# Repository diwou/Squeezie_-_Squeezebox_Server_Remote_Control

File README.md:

# Squeezie

ESP32-S3-basierte Fernsteuerung für einen Lyrion/Squeezebox-Medienserver mit ILI9488 3,5" Touchdisplay.

## Projekt-Metadaten

- **Repository**: https://codeberg.org/diwou/Squeezie_-_Squeezebox_Server_Remote_Control
- **Lizenz**: CC BY-NC-SA 4.0
- **Version**: v0.5.0

## Hardware

| Komponente | Modell |
|---|---|
| Mikrocontroller | ESP32-S3-WROOM1-N16R8 (16 MB Flash, 8 MB PSRAM) |
| Display | TN 3,5" ILI9488 SPI-TFT 480×320 |
| Touch | XPT2046 (auf Display-Modul integriert) |

### Platine

## Verkabelung

Das Display-Modul hat 14 Pins. Display-SPI und Touch-SPI sind auf getrennte GPIOs gelegt.

| Display-Pin | Bezeichnung | ESP32-S3 GPIO | Hinweis |
|---|---|---|---|
| 1 | VCC | 3,3 V | Spannungsversorgung |
| 2 | GND | GND | Masse |
| 3 | CS | GPIO 17 | LCD Chip Select |
| 4 | RST | GPIO 18 | LCD Reset |
| 5 | DC/OC | GPIO 9 | Data/Command |
| 6 | SDI | GPIO 3 | Display MOSI |
| 7 | SCK | GPIO 46 | Display SPI-Takt |
| 8 | BL | GPIO 9 | Hintergrundbeleuchtung (HIGH = an) |
| 9 | SDO | GPIO 10 | Display MISO (optional) |
| 10 | TCK | GPIO 11 | Touch SPI-Takt |
| 11 | TCS | GPIO 12 | Touch Chip Select |
| 12 | TDI | GPIO 13 | Touch MOSI |
| 13 | TDO | GPIO 14 | Touch MISO |
| 14 | PEN | GPIO 21 | Touch-Interrupt (IRQ) |

## Software-Einrichtung

### Voraussetzungen

- [PlatformIO](https://platformio.org/) (VSCodium/VSCode Extension oder CLI)

### Erstmalige Einrichtung

```bash
# Bibliotheken installieren und kompilieren
pio run

# Auf den ESP32 flashen (USB angeschlossen)
pio run --target upload

# Serielle Konsole öffnen
pio device monitor
```

### WLAN-Konfiguration

Beim ersten Start öffnet das Gerät einen Access Point **Squeezie-Setup**. Im Browser
`192.168.4.1` aufrufen und WLAN-Zugangsdaten eingeben. Nach dem Verbinden mit dem
Heimnetz erscheint die IP-Adresse auf dem Display.

### Touch-Kalibrierung

Beim allerersten Start erscheint automatisch die Kalibrierung. Es werden 3 Kreuzmarkierungen
nacheinander angezeigt, die mit dem Finger berührt werden müssen.

Die Kalibrierungsdaten werden im NVS (Flash) gespeichert und bei jedem Neustart geladen.

**Neu kalibrieren:** Obere linke Ecke des Displays 3 Sekunden gedrückt halten.

## Aktueller Stand — v0.5.0

### Player-Screen (Touch-Display)

- **Cover-Art** (128×128 px, vom LMS-Server geladen)
- **Titelanzeige**: Titel (scrollend), Interpret, Album, Tracknummer / Gesamtdauer
- **Fortschrittsbalken** mit Zeitanzeige, antippen zum Seekten
- **Transport-Buttons**: |< / Pause/Play / >|
- **Lautstärke**: Balken mit [−] / [+], Halten wiederholt
- **Gruppenlautstärke**: Bei synchronisierten Lyrion-Playern werden Lautstärkeänderungen auf die ganze Sync-Gruppe angewendet und lassen sich in den Einstellungen ein- oder ausschalten
- **Modus-Buttons**: Wiederholen (aus / Titel / Liste) und Zufall (an/aus)
- **Uhrzeit** (NTP) in der Statuszeile
- **Einstellungs-Screen**: Server-Suche per UDP-Discovery, Player-Auswahl, Sync-Lautstärke-Schalter

### Webinterface (Browser)

- **Player-Steuerung** (`http://<ip>/`): Titel, Cover, Fortschrittsbalken, Transport, Lautstärke, Modus
- **Einstellungen** (`/settings`): WLAN, Netzwerk (DHCP/Statisch), NTP, Squeezebox-Server, Player-Auswahl
- **OTA-Firmware-Update** (`/update`)
- **Log** (`/log`): Ring-Buffer mit den letzten 20 Systemereignissen

### Technisches

- **Lyrion/Squeezebox JSON-RPC API**: Play/Pause/Next/Prev/Seek/Lautstärke/Wiederholen/Zufall
- **Server-Discovery**: UDP Slim-Discovery auf Port 3483, mDNS-Service-Discovery als Fallback
- **NVS-Persistenz**: alle Einstellungen überleben einen Neustart
- **Cover-Download**: asynchroner FreeRTOS-Task (blockiert die Main-Loop nicht)
- **Selektives Display-Rendering**: nur geänderte Felder werden neu gezeichnet

## Web-Firmware-Installer (Codeberg Page)

Der Firmware-Installer über Browser ist auf der Codeberg-Page verfügbar:

- [Web-Installer öffnen](https://diwou.codeberg.page/Squeezie_-_Squeezebox_Server_Remote_Control/)

## Geplante Funktionen

- [ ] IR-Fernbedienung (Hardware-Erweiterung)

## Lizenz

[CC BY-NC-SA 4.0](https://creativecommons.org/licenses/by-nc-sa/4.0/) — Namensnennung,
nicht-kommerziell, Weitergabe unter gleichen Bedingungen.

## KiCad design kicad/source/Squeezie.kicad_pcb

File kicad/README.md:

# KiCad Hardware

Dieses Verzeichnis enthält die Platinenquellen und die exportierten Fertigungsdaten für Squeezie.

## Struktur

- `source/` - bearbeitbare KiCad-Quellen für Revision `rev0.1`
- `fab/rev0.1/bom/` - BOM, Designatoren, Positionen und Netlist
- `fab/rev0.1/Squeezie_Squeezseboxserver_Control_0.1.zip` - komplettes Fertigungspaket für den Bestelldienstleister

## Kurz-BOM

_Abgeleitet aus `fab/rev0.1/bom/bom.csv`. Wenn sich die Platine ändert, diese Übersicht gemeinsam mit der Stückliste prüfen._

| Bereich | Bauteile | Bauform | Menge | Zweck |
|---|---|---|---:|---|
| MCU | `U2` ESP32-S3-WROOM-1 | ESP32-S3-WROOM-1 | 1 | Hauptprozessor, WLAN, Steuerlogik |
| Anzeige / Anschluss | `J1` USB-C, `J2` ILI9488 Display | USB_C_Receptacle_HCTL_HC-TYPE-C-16P-01A, PinSocket_1x14_P2.54mm_Vertical | 2 | USB- und Display-Anschluss |
| Bedienung | `SW1` Boot, `SW2` Reset, `SW3` Prev, `SW4` Next, `SW5` Play, `SW6` Vol-, `SW7` Vol+, `SW8` Mute | SWITCH_FSMARA | 8 | Bedienelemente für den Player |
| Spannungsversorgung | `U1` TLV76133DCY, `D2` SS14, `D1` PWR | SOT-223-3_TabPin2, D_SMA, 0805 | 3 | 3,3-V-Regler, Schutzdiode, Power-LED |
| Widerstände | `R1` 1k, `R2/R3` 5,1k, `R4/R5/R6/R7/R8/R9/R10` 10k | 0805 | 10 | Pullups und Signalbegrenzung |
| Kondensatoren | `C1/C2` 10µ, `C3` 10µ, `C5` 1µ, `C4/C6/C7/C10/C11/C12/C13/C14/C15` 100n | 1206, 0805 | 12 | Abblockung und Pufferung |

## Hinweise

- `H1` bis `H4` sind Montagebohrungen und tauchen deshalb nicht in der BOM-CSV auf.
- Die vollständige, exportierte Stückliste liegt zusätzlich als CSV unter `fab/rev0.1/bom/`.
- `source/*.kicad_prl` und `source/fp-info-cache` sind lokale bzw. generierte Dateien und werden per `.gitignore` ausgeschlossen.
- Das Projekt wird im gleichen Schema gepflegt wie der HUB75-KiCad-Stand.

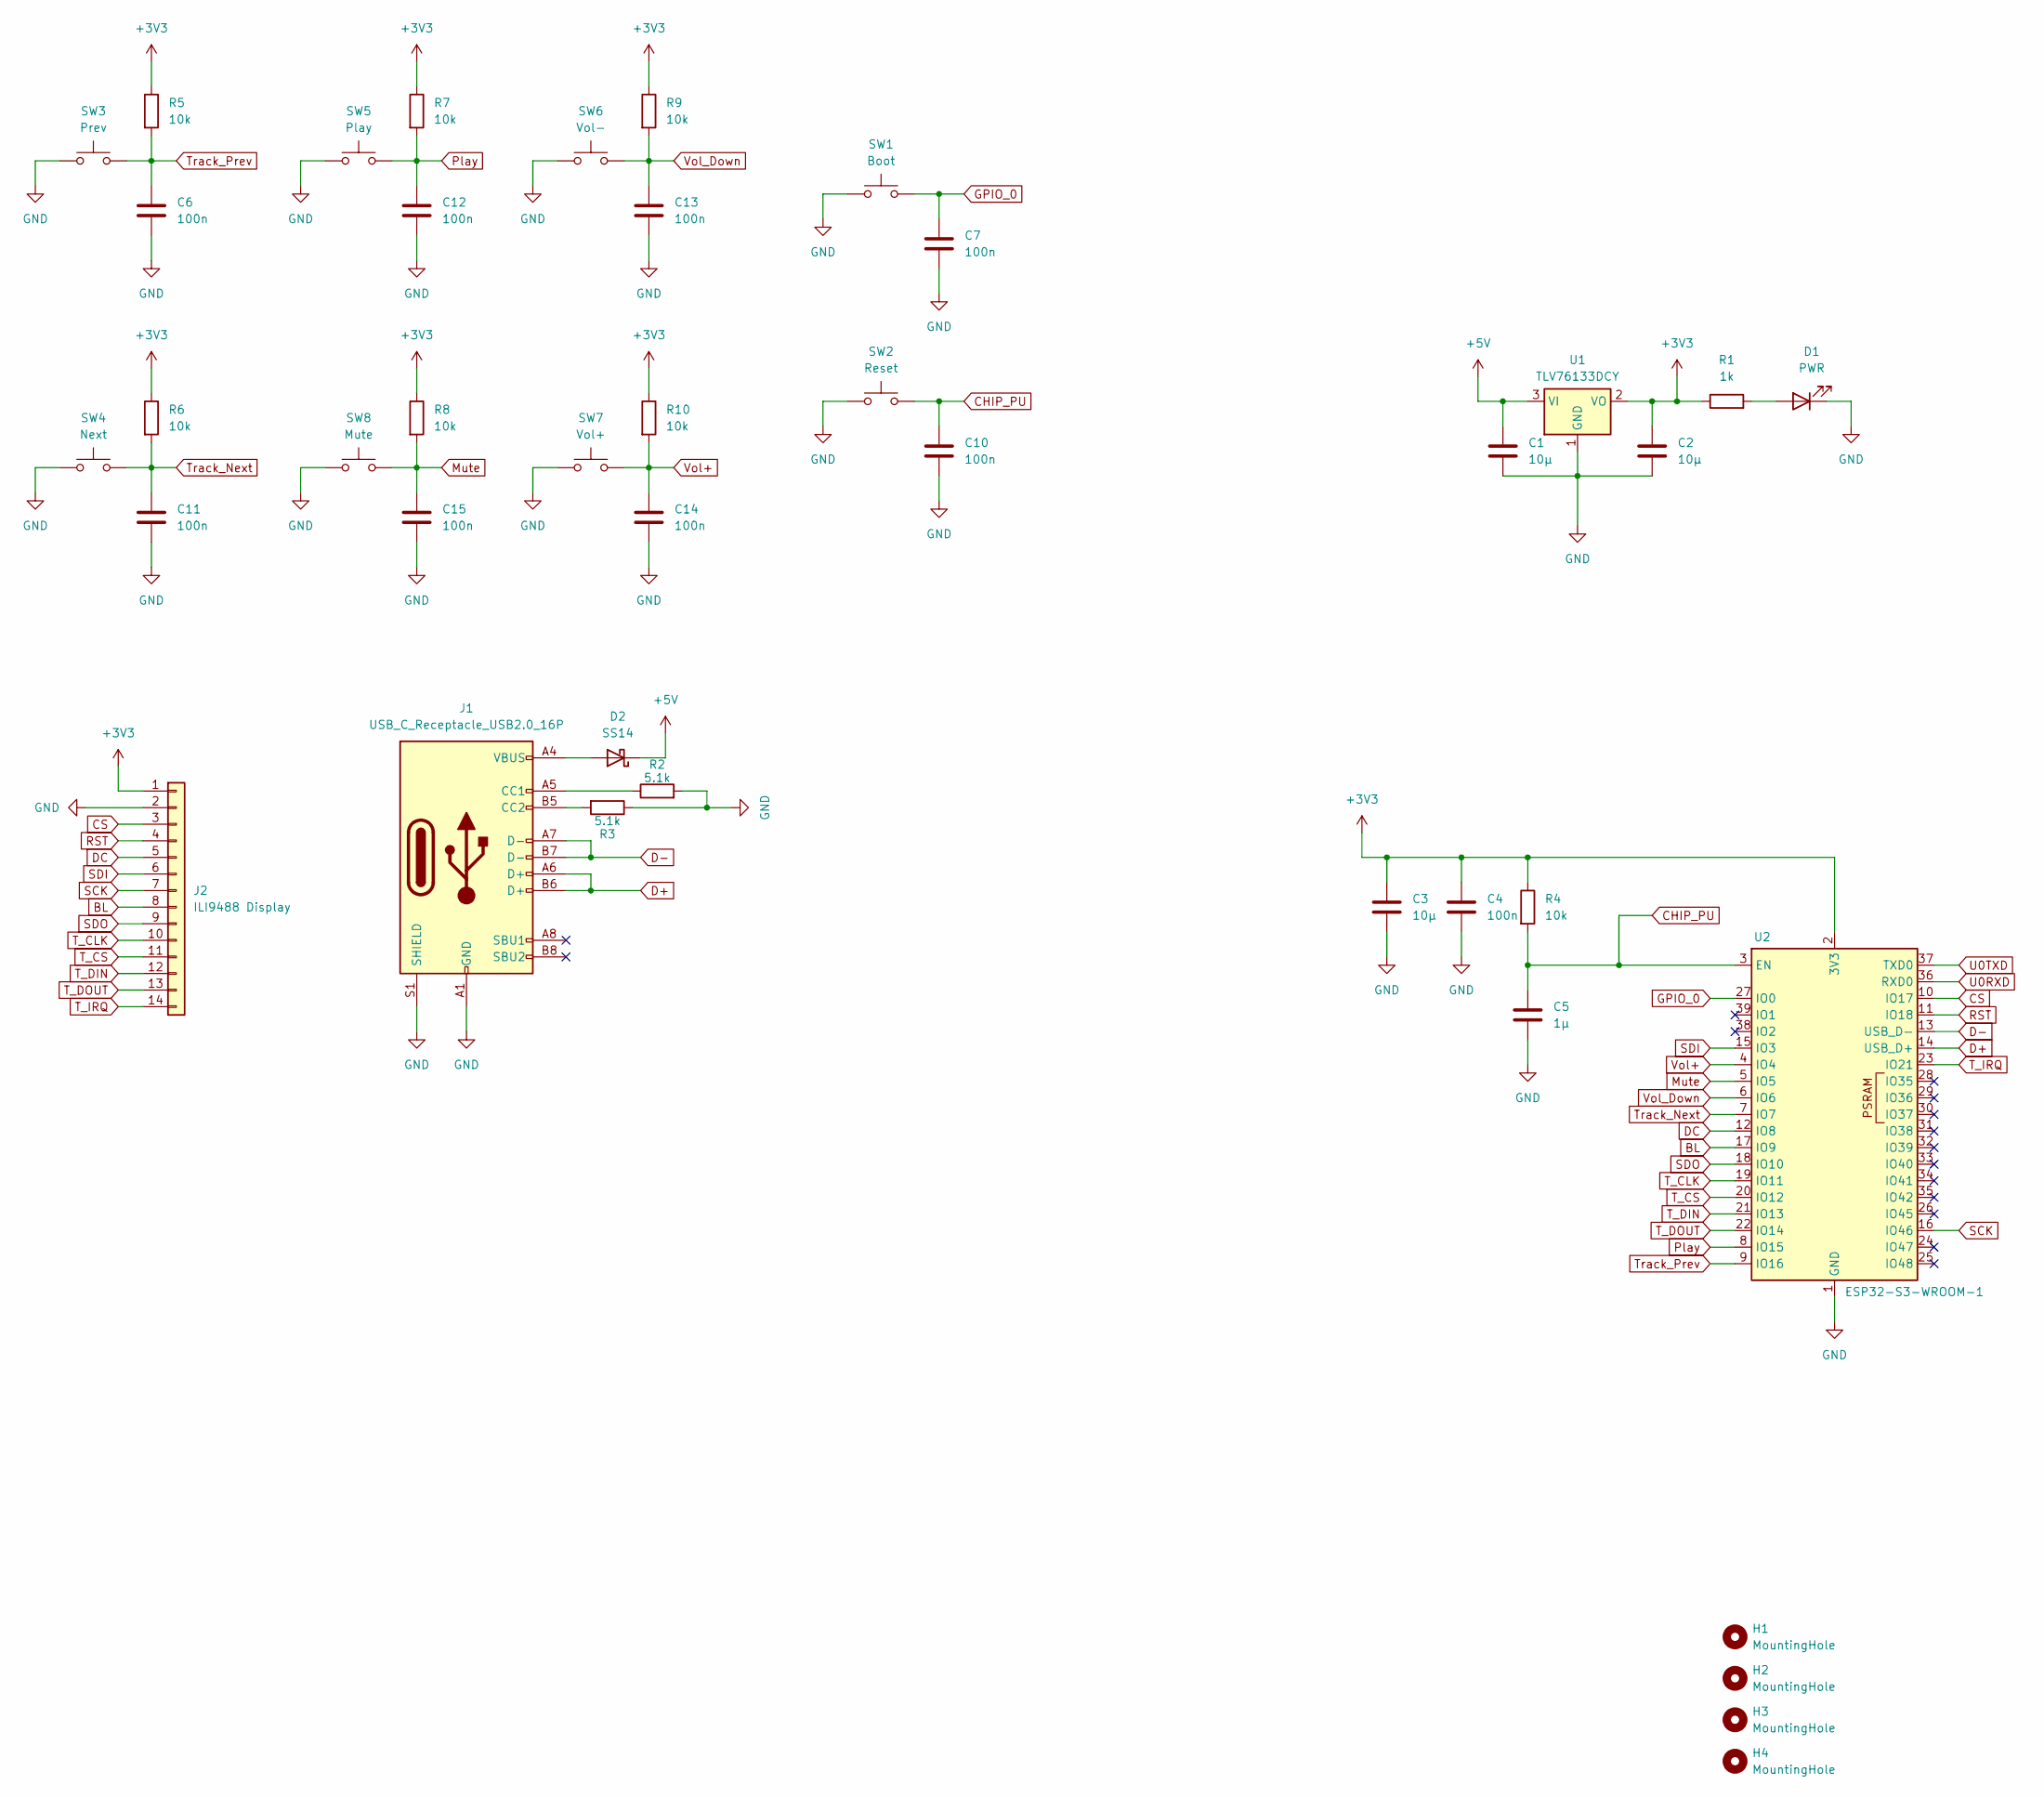
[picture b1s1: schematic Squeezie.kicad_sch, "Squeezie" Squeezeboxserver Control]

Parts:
C1, C2: 10µ; C_1206_3216Metric_Pad1.33x1.80mm_HandSolder
C3: 10µ; C_0805_2012Metric_Pad1.18x1.45mm_HandSolder
C4, C6, C7, C10, C11, C12, C13, C14, C15: 100n; C_0805_2012Metric_Pad1.18x1.45mm_HandSolder
C5: 1µ; C_0805_2012Metric_Pad1.18x1.45mm_HandSolder
D1: PWR; LED_0805_2012Metric_Pad1.15x1.40mm_HandSolder
D2: SS14; D_SMA
H1, H2, H3, H4: MountingHole; MountingHole_3.5mm
J1: USB_C_Receptacle_USB2.0_16P; USB_C_Receptacle_HCTL_HC-TYPE-C-16P-01A
J2: ILI9488 Display; PinSocket_1x14_P2.54mm_Vertical
R1: 1k; R_0805_2012Metric_Pad1.20x1.40mm_HandSolder
R2, R3: 5.1k; R_0805_2012Metric_Pad1.20x1.40mm_HandSolder
R4, R5, R6, R7, R8, R9, R10: 10k; R_0805_2012Metric_Pad1.20x1.40mm_HandSolder
SW1: Boot; SWITCH_FSMARA
SW2: Reset; SWITCH_FSMARA
SW3: Prev; SWITCH_FSMARA
SW4: Next; SWITCH_FSMARA
SW5: Play; SWITCH_FSMARA
SW6: Vol-; SWITCH_FSMARA
SW7: Vol+; SWITCH_FSMARA
SW8: Mute; SWITCH_FSMARA
U1: TLV76133DCY; SOT-223-3_TabPin2
U2: ESP32-S3-WROOM-1

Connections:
+3V3: C2.1, C3.1, C4.1, J2.1, R1.1, R4.1, R5.1, R6.1, R7.1, R8.1, R9.1, R10.1, U1.2 (VO), U2.2 (3V3)
+5V: C1.1, D2.1 (K), U1.3 (VI)
BL: J2.8, U2.17 (IO9)
CHIP_PU: C5.1, C10.1, R4.2, SW2.2, U2.3 (EN)
CS: J2.3, U2.10 (IO17)
D+: J1.A6 (D+), J1.B6 (D+), U2.14 (USB_D+)
D-: J1.A7 (D-), J1.B7 (D-), U2.13 (USB_D-)
DC: J2.5, U2.12 (IO8)
GND: C1.2, C2.2, C3.2, C4.2, C5.2, C6.2, C7.2, C10.2, C11.2, C12.2, C13.2, C14.2, C15.2, D1.1 (K), J1.A1 (GND), J1.A12 (GND), J1.B1 (GND), J1.B12 (GND), J1.S1 (SHIELD), J2.2, R2.2, R3.1, SW1.1, SW1.GND, SW2.1, SW2.GND, SW3.1, SW3.GND, SW4.1, SW4.GND, SW5.1, SW5.GND, SW6.1, SW6.GND, SW7.1, SW7.GND, SW8.1, SW8.GND, U1.1 (GND), U2.1 (GND), U2.40 (GND), U2.41 (GND)
GPIO_0: C7.1, SW1.2, U2.27 (IO0)
Mute: C15.1, R8.2, SW8.2, U2.5 (IO5)
unnamed: D1.2 (A), R1.2
unnamed: D2.2 (A), J1.A4 (VBUS), J1.A9 (VBUS), J1.B4 (VBUS), J1.B9 (VBUS)
unnamed: J1.A5 (CC1), R2.1
unnamed: J1.B5 (CC2), R3.2
Play: C12.1, R7.2, SW5.2, U2.8 (IO15)
RST: J2.4, U2.11 (IO18)
SCK: J2.7, U2.16 (IO46)
SDI: J2.6, U2.15 (IO3)
SDO: J2.9, U2.18 (IO10)
T_CLK: J2.10, U2.19 (IO11)
T_CS: J2.11, U2.20 (IO12)
T_DIN: J2.12, U2.21 (IO13)
T_DOUT: J2.13, U2.22 (IO14)
T_IRQ: J2.14, U2.23 (IO21)
Track_Next: C11.1, R6.2, SW4.2, U2.7 (IO7)
Track_Prev: C6.1, R5.2, SW3.2, U2.9 (IO16)
U0RXD: U2.36 (RXD0)
U0TXD: U2.37 (TXD0)
Vol+: C14.1, R10.2, SW7.2, U2.4 (IO4)
Vol_Down: C13.1, R9.2, SW6.2, U2.6 (IO6)

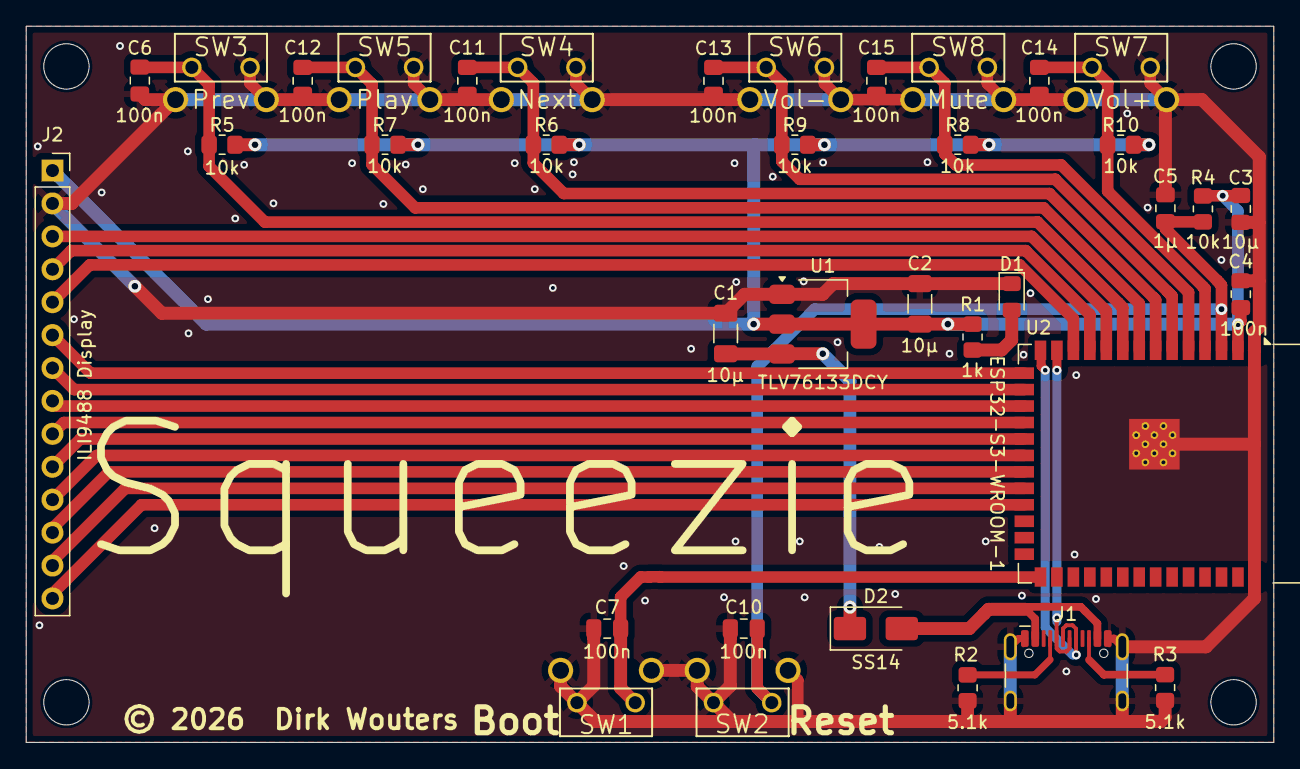
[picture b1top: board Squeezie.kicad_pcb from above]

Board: 2 copper layers, 96.3 x 55.3 mm, 41 parts (0 on the bottom side), 29 nets.

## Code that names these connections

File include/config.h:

#pragma once

// =============================================================================
// Squeezie — Zentrale Konfiguration
// =============================================================================

// --- Anwendung ---
#define APP_VERSION_BASE "0.5.0"
#if __has_include("version_generated.h")
#include "version_generated.h"
#endif
#ifndef APP_VERSION
#define APP_VERSION APP_VERSION_BASE
#endif

// --- Pins ---
#define PIN_TFT_BL      9   // Hintergrundbeleuchtung (HIGH = an)
#define PIN_TFT_CS      17  // Display Chip-Select
#define PIN_TFT_DC      8   // Display Data/Command
#define PIN_TFT_RST     18  // Display Reset
#define PIN_TFT_MOSI    3   // Display SDI / MOSI (SPI)
#define PIN_TFT_MISO    10  // Display SDO / MISO (SPI, optional read-back)
#define PIN_TFT_SCLK    46  // Display SCK (SPI)
#define PIN_TOUCH_CS    12  // Touch Chip-Select (TCS)
#define PIN_TOUCH_IRQ   21  // Touch-Interrupt (PEN, LOW = berührt)
#define PIN_TOUCH_MOSI  13  // Touch T_DIN / MOSI (SPI)
#define PIN_TOUCH_MISO  14  // Touch T_DOUT / MISO (SPI)
#define PIN_TOUCH_SCLK  11  // Touch T_CLK / SCK (SPI)
#define PIN_BOOT_BTN    0   // Eingebauter BOOT-Button (LOW = gedrückt)
#define PIN_PLAY_BTN    15  // Externer Play/Pause-Taster (LOW = gedrückt)
#define PIN_PREV_BTN    16  // Externer Track-zurueck-Taster (LOW = gedrückt)
#define PIN_NEXT_BTN    7   // Externer Track-vor-Taster (LOW = gedrückt)
#define PIN_VOL_UP_BTN  4   // Externer Volume-Plus-Taster (LOW = gedrückt)
#define PIN_VOL_DN_BTN  6   // Externer Volume-Minus-Taster (LOW = gedrückt)
#define PIN_MUTE_BTN    5   // Externer Mute-Taster (LOW = gedrückt)

// --- Display ---
#define DISPLAY_ROTATION    1   // 1 = Querformat: 480×320
#define DISPLAY_WIDTH     480
#define DISPLAY_HEIGHT    320

// --- NVS ---
#define NVS_NAMESPACE        "squeezie"
#define NVS_KEY_CAL_OK       "calOK"    // bool: Kalibrierung gültig
#define NVS_KEY_CAL_X0       "calX0"    // int16: Rohwert Bildschirm-X am linken Zielpunkt
#define NVS_KEY_CAL_X1       "calX1"    // int16: Rohwert Bildschirm-X am rechten Zielpunkt
#define NVS_KEY_CAL_Y0       "calY0"    // int16: Rohwert Bildschirm-Y am oberen Zielpunkt
#define NVS_KEY_CAL_Y1       "calY1"    // int16: Rohwert Bildschirm-Y am unteren Zielpunkt
#define NVS_KEY_CAL_SWAP     "calSwap"  // uint8: 1 = X/Y-Kanäle getauscht

// --- Kalibrierungszielpunkte (Bildschirmkoordinaten) ---
#define CAL_X_LEFT    30
#define CAL_X_RIGHT   (DISPLAY_WIDTH  - 30)
#define CAL_Y_TOP     30
#define CAL_Y_BOTTOM  (DISPLAY_HEIGHT - 30)

// --- WiFi / Netzwerk (NVS-Schlüssel) ---
#define NVS_KEY_WIFI_SSID   "wifiSSID"
#define NVS_KEY_WIFI_PASS   "wifiPass"
#define NVS_KEY_NET_DHCP    "netDHCP"
#define NVS_KEY_NET_IP      "netIP"
#define NVS_KEY_NET_MASK    "netMask"
#define NVS_KEY_NET_GW      "netGW"
#define NVS_KEY_NET_DNS     "netDNS"
#define NVS_KEY_NET_NTP     "netNTP"

// --- Squeezebox Server (NVS-Schlüssel) ---
#define NVS_KEY_SRV_HOST    "srvHost"
#define NVS_KEY_SRV_PORT    "srvPort"
#define NVS_KEY_PLAYER_MAC  "playerMAC"
#define NVS_KEY_SYNC_VOL    "syncVol"
#define NVS_KEY_SCROLL_SPD  "scrollSpd"
#define NVS_KEY_PL_ID       "plId"
#define NVS_KEY_PL_NAME     "plName"

// --- WiFi AP ---
#define WIFI_AP_SSID             "Squeezie-Setup"
#define WIFI_CONNECT_TIMEOUT_MS  8000
#define LYRION_DEFAULT_PORT      9000

// --- OTA / Sicherheit ---
#define OTA_HOSTNAME             "squeezie"
#define OTA_PASSWORD             "squeezie"

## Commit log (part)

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2026-04-05 Initial commit: ESP32-S3 Squeezebox remote control
    ESP32-S3-WROOM1-N16R8 mit ILI9488 3.5" Touchdisplay (LovyanGFX),
    ESPAsyncWebServer, Lyrion/Squeezebox API-Anbindung (in Arbeit).
    Lizenz: CC BY-NC-SA 4.0
2026-04-05 docs: README auf v0.3.2 aktualisiert, Lizenz auf CC BY-NC-SA 4.0
2026-04-05 Factory Reset via BOOT-Button
2026-04-07 Release 0.3.3
2026-04-07 Release 0.4.0
2026-04-07 Clean up release metadata
2026-04-09 Add playlist selection in settings and display mute control
2026-04-11 Fix LMS mute handling and add cspell setup
2026-04-11 Update changelog commit references
2026-04-11 Add automatic firmware export
2026-04-11 Update changelog firmware export reference
2026-04-20 Fix cover stability and document 0.4.2
2026-04-20 Unify development versioning and fix prefetch
2026-04-21 Add configurable sync volume handling
2026-04-22 fix: Bedienung reaktionsschneller machen
2026-04-22 fix: externe Lautstärkeänderungen stabilisieren
2026-04-22 fix: Sync-Player absolut nachführen
2026-04-23 docs: KiCad-Squeezie im HUB75-Schema ablegen
2026-04-23 docs: Changelog-Referenz für KiCad-Import ergänzen
2026-04-25 fix: Cover-Download und Regeln stabilisieren
2026-04-28 PlatformIO stabilisieren
2026-04-29 feat: Code-Review-Punkte umgesetzt
    - display.cpp in 4 Module aufgeteilt (display_draw, display_touch,
    display_cover, display_screens) + interner Header display_intern.h
    - HW-Watchdog (esp_task_wdt_init) in setup() aktiviert
    - Doxygen-Kommentare zu allen öffentlichen API-Headern ergänzt
    - OTA-Passwortschutz über config.h (OTA_PASSWORD) aktiviert
    - NVS-Kalibrierungsdaten: Namespace-Konflikt behoben
2026-04-29 fix: Watchdog-Bootloop durch fehlendes Feeding behoben
    Der HW-Watchdog (esp_task_wdt_init(10, true)) führte zu einem Bootloop,
    weil loop() und coverDlTask() den Watchdog nicht regelmässig feedeten.
    - esp_task_wdt_add(nullptr) + esp_task_wdt_reset() in loop()
    - esp_task_wdt_reset() während readHttpBody() (HTTP-Download)
    - esp_task_wdt_reset() nach HTTP-Download in coverDlTask()
    Referenz: watchdog-bootloop-20260429
2026-04-29 fix: Cover-Download-Task-Handle und Watchdog-Bootloop endgültig behoben
    - in coverDlTask() entfernt: das Task-Handle
    bleibt erhalten, sodass displayPreloadCover() weiterhin Notifications
    senden kann (bisher nur erster Cover-Download funktionierte).
    - coverDlTask() und prefetchTask() auf ulTaskNotifyTake mit 2s-Timeout
    umgestellt: blockierte Tasks mit esp_task_wdt_add() führten nach 10s
    zu Watchdog-Reset → ESP-Reboot-Loop.
2026-04-29 fix: Prefetch vollständig entfernt und Cover-Wechsel-Dedup repariert
    - Prefetch-Mechanismus komplett entfernt (prefetchTask, displayQueuePrefetch,
    PrefetchSlot, PSRAM-Puffer, SQUEEZE_PREFETCH-Konstante), da er wiederholt
    Probleme mit konkurrierenden HTTP-Downloads und Task-Interferenzen verursachte.
    - LMS-Poll fragt nur noch aktuellen Titel ab statt SQUEEZE_PREFETCH+1 Einträge.
    - URL-Dedup in displayPreloadCover() auf URL+Key-Vergleich umgestellt:
    bisher blockierte die identische /music/current/…-URL jeden weiteren
2026-04-29 docs: Changelog-Referenzen auf aktuellen Commit-Hash aktualisiert
2026-04-29 docs: Preload-zu-Notification-Umstellung im Changelog dokumentiert
    - Expliziter Eintrag, dass das Single-Shot-Preload durch persistenten
    Notification-basierten coverDlTask ersetzt wurde.
2026-04-29 fix: OTA-Authentifizierung durch upload_flags in platformio.ini ergänzt
    - upload_flags=--auth=squeezie in der [env:…_ota]-Sektion hinzugefügt,
    damit das OTA-Passwort aus config.h beim Upload mitgesendet wird.
    - Der Code-Review hatte ArduinoOTA.setPassword() aktiviert, aber die
    platformio.ini nicht mit angepasst.
2026-04-29 fix: Single-Shot-Cover-Download wiederhergestellt (Latenz-Probleme)
    - Persistenten Notification-Task (Code-Review) rückgängig gemacht:
    displayPreloadCover() erzeugt wieder einen eigenen FreeRTOS-Task pro
    Cover-Download, der nach der Übertragung terminiert.
    - HTTP-Timeouts auf alte Werte zurückgesetzt (3000ms Gesamt, 1200ms
    pro Read), da die erhöhten Timeouts (8000ms/5000ms) Latenzen
    verursachten.
2026-04-29 docs: Changelog-Hash auf aktuellen Commit aktualisiert
2026-04-29 fix: coverDlTask nicht mehr zum Watchdog hinzugefügt
    - esp_task_wdt_add() aus coverDlTask entfernt: der Single-Shot-Task läuft
    nur kurz (HTTP-Timeout 3s), feedt während readHttpBody() und terminiert
    sich selbst. Ein eigener Watchdog-Eintrag ist nicht nötig und verursachte
    OTA-Abbrüche (der Watchdog erwartete Feeding von einem nicht mehr
    existierenden Task).
2026-04-29 fix: Watchdog-Init nach webserverInit() verschoben
    - esp_task_wdt_init() in setup() steht jetzt erst NACH webserverInit(),
    da connectWiFi() bis zu 12 s blockieren kann (8 s + 4 s Retry).
    Der Watchdog (10 s) hätte während der WLAN-Verbindung in setup()
    einen Neustart ausgelöst.
    - Gegenmassnahme für die zyklischen Reboots und OTA-Abbrüche.
2026-04-29 fix: OTA-Fortschritt entkoppeln
2026-04-29 fix: ArduinoOTA-Watchdog pausieren
2026-04-29 fix: Steuerbefehle schneller priorisieren
2026-05-01 fix: OTA-Anzeige wieder sofort zeichnen
2026-05-01 docs: Changelog-Referenzen und OTA-Fix ergänzen
2026-05-01 fix: Display-Text für türkische Glyphen fallbacken
2026-05-01 docs: Changelog um Display-Glyphen-Fix ergänzen
2026-05-01 fix: Display-Cover auf schnellen Pfad zurücksetzen
2026-05-01 docs: Display-Cover-Fix im Changelog ergänzen
2026-05-01 fix: Lautstärkebuttons im Player-Screen wieder einblenden
2026-05-01 docs: Lautstärke-Buttons im Changelog ergänzen
2026-05-01 fix: Browser-Cover direkt auf 512er LMS-URL umstellen
2026-05-01 docs: Browser-Cover-Fix im Changelog ergänzen
2026-05-01 fix: Browser-Cover und OTA-Layout nachziehen
2026-05-01 docs: Browser-Cover und OTA-Layout im Changelog nachziehen
2026-05-01 fix: Browser-Coverfläche auf 512px erweitern
2026-05-01 fix: Browser-Cover über lokalen Proxy ausliefern
2026-05-01 docs: Browser-Cover-Proxy im Changelog ergänzen
2026-05-01 fix: Browser-Cover wieder direkt vom LMS laden
2026-05-01 docs: Browser-Cover-Fix im Changelog aktualisieren
2026-05-01 fix: Browser-Cover per Redirect auf LMS lenken
2026-05-01 docs: Browser-Redirect im Changelog ergänzen
2026-05-01 fix: Browser-Cover wieder direkt auf 512x512 LMS-URL
2026-05-01 fix: Browser-Cover direkt aus Status-URL speisen
2026-05-01 docs: Browser-Cover direkt aus Status-URL dokumentieren
2026-05-01 fix: Browser-Cover beim Rendern initial setzen
2026-05-01 fix: Browser-Cover im Initial-HTML setzen
2026-05-01 docs: Changelog für Browser-URL nachziehen
2026-05-01 fix: Browser-Cover auf current-URL zurückführen
2026-05-01 fix: Browser-Cover sichtbar laden
2026-05-01 docs: Browser-Cover-Fix im Changelog vermerken
2026-05-01 fix: Browser-Cover-Startwert stabilisieren
2026-05-01 fix: Browser-Cover per JS initialisieren
2026-05-01 docs: Browser-Cover-Startfix dokumentieren
2026-05-01 fix: Browser-Cover wieder direkt setzen
2026-05-01 docs: Browser-Cover-Direktlink dokumentieren
2026-05-01 fix: Browser-Cover als Overlay rendern
2026-05-01 docs: Overlay-Fix im Changelog vermerken
2026-05-01 fix: Browser-Cover über Platzhalter legen
2026-05-01 docs: Browser-Overlay-Fix dokumentieren
2026-05-01 fix: Browser-Cover als Hintergrund laden
2026-05-01 docs: Browser-Hintergrundpfad dokumentieren
2026-05-02 fix: Browser-Cover wieder als Proxy ausliefern
2026-05-03 fix: LMS-Poll für Cover-Updates verkürzen
2026-05-03 docs: Changelog für Poll-Verkürzung referenzieren
2026-05-04 fix: Player-Screen nach Langläufen stabilisieren
2026-05-04 docs: Changelog um Langläufer-Fix ergänzen
2026-05-09 fix: Cover-Downloads bei Timeout beenden
2026-05-09 docs: Changelog um Cover-Fix-Referenz ergänzen
2026-05-12 fix: aktualisiere pinmapping, touch-spi und serversuche
2026-05-12 docs(changelog): ersetze arbeits-ids durch commit-hash
2026-05-12 fix: verbessere lms discovery und erweitere hardware-tasten
2026-05-12 docs(changelog): hinterlege commit-id fuer neue eintraege
2026-05-12 feat: release-vorbereitung mit web-installer und discovery-fixes
2026-05-12 docs(changelog): setze commit-referenzen fuer release-block
2026-05-12 Deploy Web-Installer page
2026-05-12 docs: ergänze projektbilder und web-installer-link
2026-05-12 docs(changelog): setze commit-id für bild-update
2026-05-14 chore: entferne AGENTS.md aus dem Repository
2026-05-19 fix(display): stabilisiere Lauftext-Rendering und zeige Uptime im Webinterface
2026-05-19 docs(changelog): ergänze Commit-Referenzen für Lauftext und Uptime
2026-05-19 fix(lms): härte json-rpc payload und sync-member parsing
2026-05-19 docs(changelog): ergänze commit-id für lms-jsonrpc-fix

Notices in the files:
kicad/source/Squeezie.kicad_pcb:
© 2026  Dirk Wouters
License: CC BY-NC-SA 4.0
